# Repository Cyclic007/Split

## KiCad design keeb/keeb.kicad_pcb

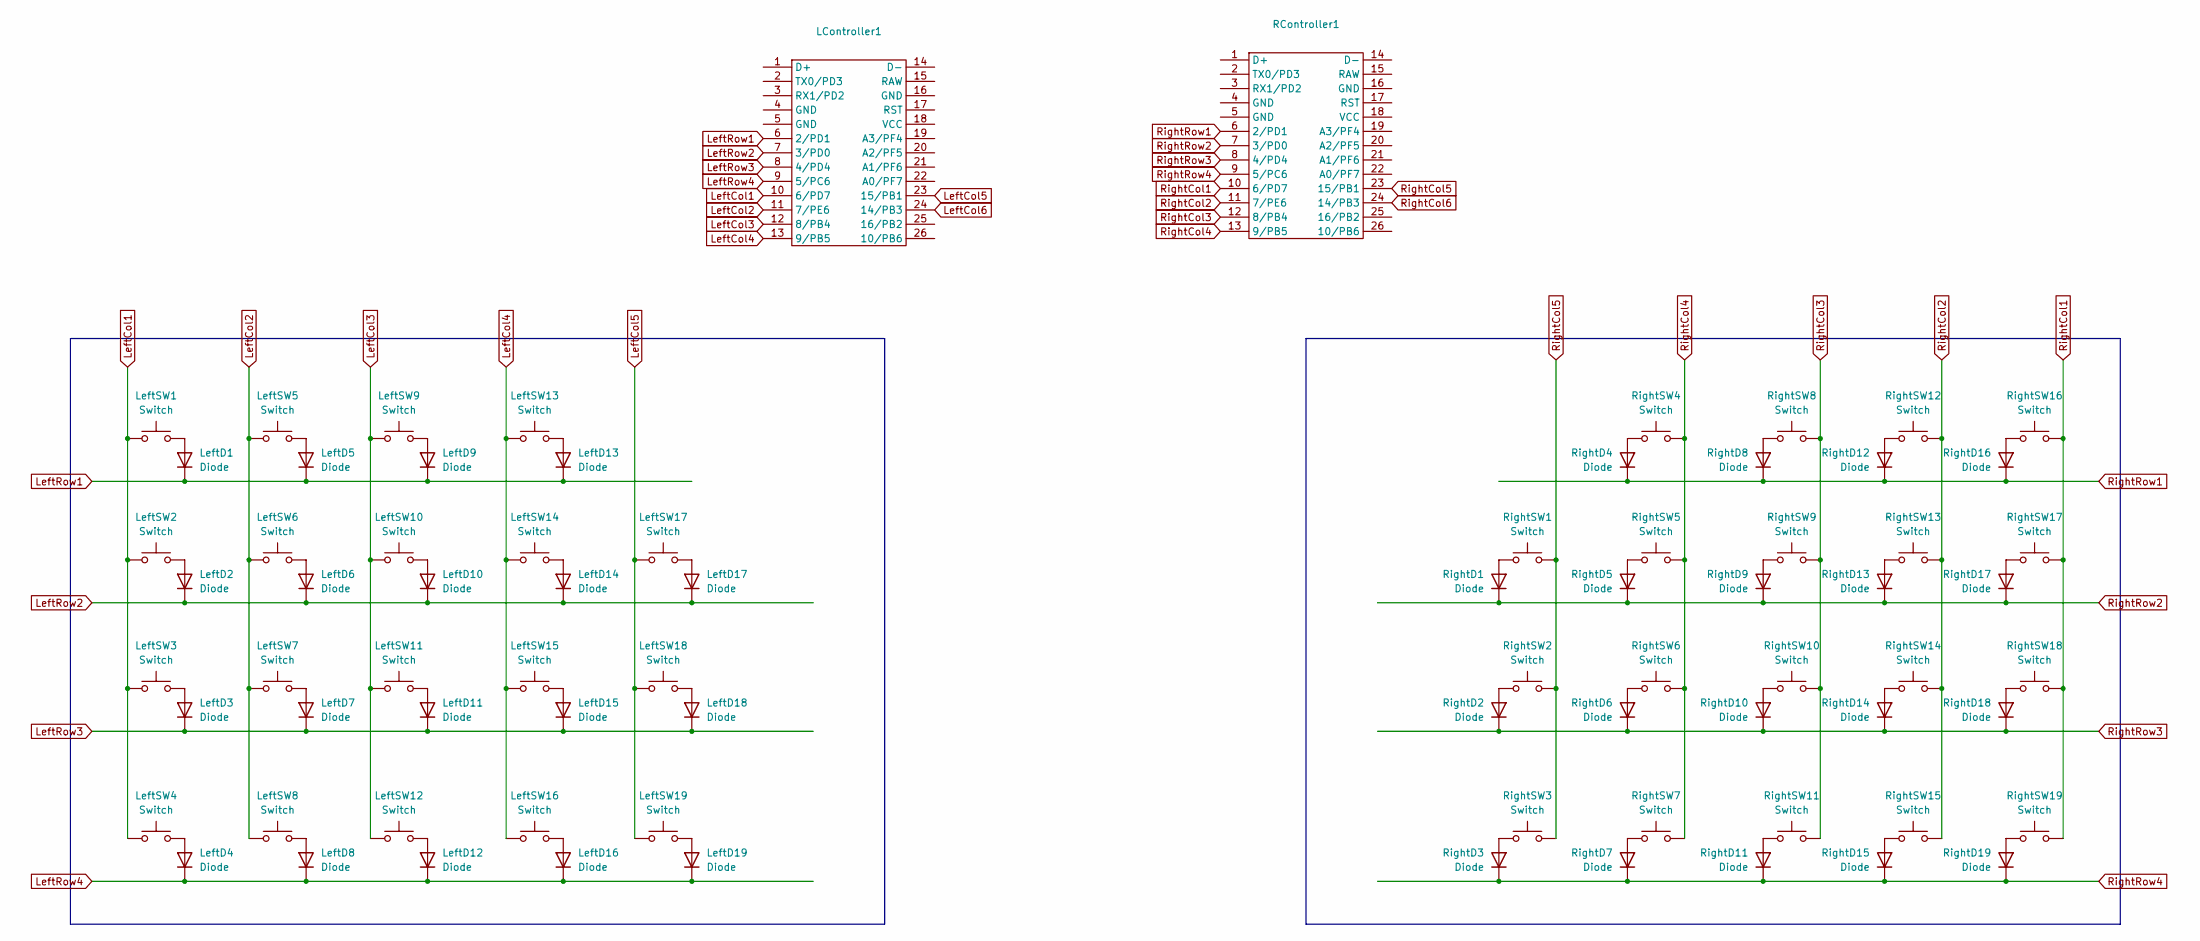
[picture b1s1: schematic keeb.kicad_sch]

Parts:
LController1: Adafruit_KB2040
LeftD1, LeftD2, LeftD3, LeftD4, LeftD5, LeftD6, LeftD7, LeftD8, LeftD9, LeftD10, LeftD11, LeftD12, LeftD13, LeftD14, LeftD15, LeftD16, LeftD17, LeftD18, LeftD19: Diode; D_DO-35_SOD27_P7.62mm_Horizontal
LeftSW1, LeftSW2, LeftSW3, LeftSW4, LeftSW5, LeftSW6, LeftSW7, LeftSW8, LeftSW9, LeftSW10, LeftSW11, LeftSW12, LeftSW13, LeftSW14, LeftSW15, LeftSW16, LeftSW17, LeftSW18, LeftSW19: Switch; MX_PCB_1.00u
RController1: Adafruit_KB2040
RightD1, RightD2, RightD3, RightD4, RightD5, RightD6, RightD7, RightD8, RightD9, RightD10, RightD11, RightD12, RightD13, RightD14, RightD15, RightD16, RightD17, RightD18, RightD19: Diode; D_DO-35_SOD27_P7.62mm_Horizontal
RightSW1, RightSW2, RightSW3, RightSW4, RightSW5, RightSW6, RightSW7, RightSW8, RightSW9, RightSW10, RightSW11, RightSW12, RightSW13, RightSW14, RightSW15, RightSW16, RightSW17, RightSW18, RightSW19: Switch; MX_PCB_1.00u

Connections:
LeftCol1: LController1.10 (6/PD7), LeftSW1.1, LeftSW2.1, LeftSW3.1, LeftSW4.1
LeftCol2: LController1.11 (7/PE6), LeftSW5.1, LeftSW6.1, LeftSW7.1, LeftSW8.1
LeftCol3: LController1.12 (8/PB4), LeftSW9.1, LeftSW10.1, LeftSW11.1, LeftSW12.1
LeftCol4: LController1.13 (9/PB5), LeftSW13.1, LeftSW14.1, LeftSW15.1, LeftSW16.1
LeftCol5: LController1.23 (15/PB1), LeftSW17.1, LeftSW18.1, LeftSW19.1
LeftCol6: LController1.24 (14/PB3)
LeftRow1: LController1.6 (2/PD1), LeftD1.1 (K), LeftD5.1 (K), LeftD9.1 (K), LeftD13.1 (K)
LeftRow2: LController1.7 (3/PD0), LeftD2.1 (K), LeftD6.1 (K), LeftD10.1 (K), LeftD14.1 (K), LeftD17.1 (K)
LeftRow3: LController1.8 (4/PD4), LeftD3.1 (K), LeftD7.1 (K), LeftD11.1 (K), LeftD15.1 (K), LeftD18.1 (K)
LeftRow4: LController1.9 (5/PC6), LeftD4.1 (K), LeftD8.1 (K), LeftD12.1 (K), LeftD16.1 (K), LeftD19.1 (K)
unnamed: LeftD1.2 (A), LeftSW1.2
unnamed: LeftD2.2 (A), LeftSW2.2
unnamed: LeftD3.2 (A), LeftSW3.2
unnamed: LeftD4.2 (A), LeftSW4.2
unnamed: LeftD5.2 (A), LeftSW5.2
unnamed: LeftD6.2 (A), LeftSW6.2
unnamed: LeftD7.2 (A), LeftSW7.2
unnamed: LeftD8.2 (A), LeftSW8.2
unnamed: LeftD9.2 (A), LeftSW9.2
unnamed: LeftD10.2 (A), LeftSW10.2
unnamed: LeftD11.2 (A), LeftSW11.2
unnamed: LeftD12.2 (A), LeftSW12.2
unnamed: LeftD13.2 (A), LeftSW13.2
unnamed: LeftD14.2 (A), LeftSW14.2
unnamed: LeftD15.2 (A), LeftSW15.2
unnamed: LeftD16.2 (A), LeftSW16.2
unnamed: LeftD17.2 (A), LeftSW17.2
unnamed: LeftD18.2 (A), LeftSW18.2
unnamed: LeftD19.2 (A), LeftSW19.2
unnamed: RightD1.2 (A), RightSW1.2
unnamed: RightD2.2 (A), RightSW2.2
unnamed: RightD3.2 (A), RightSW3.2
unnamed: RightD4.2 (A), RightSW4.2
unnamed: RightD5.2 (A), RightSW5.2
unnamed: RightD6.2 (A), RightSW6.2
unnamed: RightD7.2 (A), RightSW7.2
unnamed: RightD8.2 (A), RightSW8.2
unnamed: RightD9.2 (A), RightSW9.2
unnamed: RightD10.2 (A), RightSW10.2
unnamed: RightD11.2 (A), RightSW11.2
unnamed: RightD12.2 (A), RightSW12.2
unnamed: RightD13.2 (A), RightSW13.2
unnamed: RightD14.2 (A), RightSW14.2
unnamed: RightD15.2 (A), RightSW15.2
unnamed: RightD16.2 (A), RightSW16.2
unnamed: RightD17.2 (A), RightSW17.2
unnamed: RightD18.2 (A), RightSW18.2
unnamed: RightD19.2 (A), RightSW19.2
RightCol1: RController1.10 (6/PD7), RightSW16.1, RightSW17.1, RightSW18.1, RightSW19.1
RightCol2: RController1.11 (7/PE6), RightSW12.1, RightSW13.1, RightSW14.1, RightSW15.1
RightCol3: RController1.12 (8/PB4), RightSW8.1, RightSW9.1, RightSW10.1, RightSW11.1
RightCol4: RController1.13 (9/PB5), RightSW4.1, RightSW5.1, RightSW6.1, RightSW7.1
RightCol5: RController1.23 (15/PB1), RightSW1.1, RightSW2.1, RightSW3.1
RightCol6: RController1.24 (14/PB3)
RightRow1: RController1.6 (2/PD1), RightD4.1 (K), RightD8.1 (K), RightD12.1 (K), RightD16.1 (K)
RightRow2: RController1.7 (3/PD0), RightD1.1 (K), RightD5.1 (K), RightD9.1 (K), RightD13.1 (K), RightD17.1 (K)
RightRow3: RController1.8 (4/PD4), RightD2.1 (K), RightD6.1 (K), RightD10.1 (K), RightD14.1 (K), RightD18.1 (K)
RightRow4: RController1.9 (5/PC6), RightD3.1 (K), RightD7.1 (K), RightD11.1 (K), RightD15.1 (K), RightD19.1 (K)

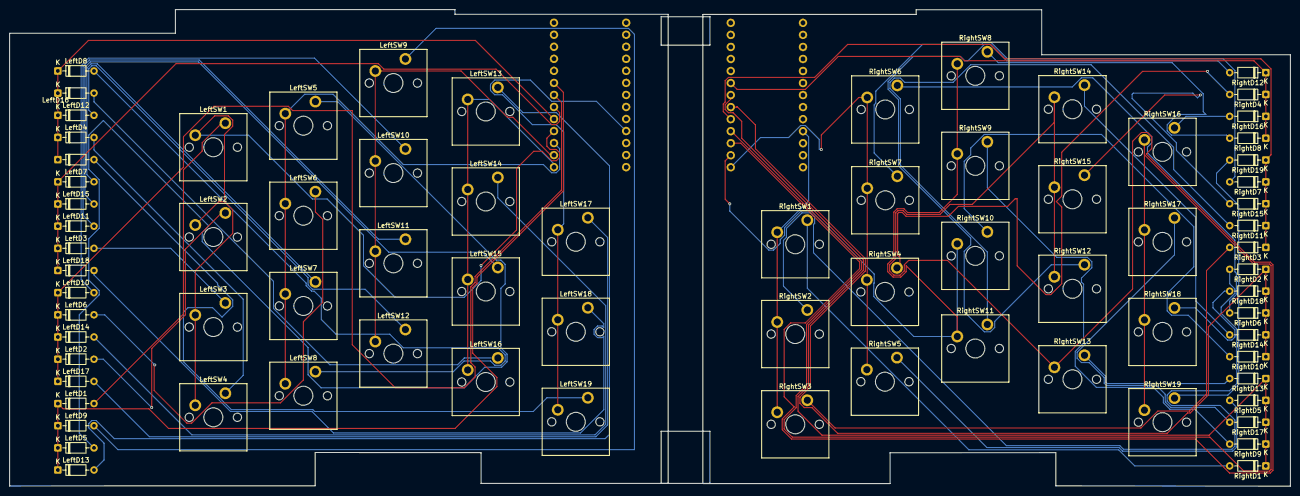
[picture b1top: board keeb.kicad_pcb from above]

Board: 2 copper layers, 270.3 x 100.6 mm, 78 parts (0 on the bottom side), 56 nets.

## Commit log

2025-10-03 setup
2025-10-04 setup schem
2025-10-07 things
